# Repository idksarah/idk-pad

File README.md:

# idkpad <br>
boink 9 key macro with 2 rotary encoders and a clear window so you can see your very nice pcb :3
## usage
3d print the included files and send the idkpad/manu.zip to your preferred manufacturer

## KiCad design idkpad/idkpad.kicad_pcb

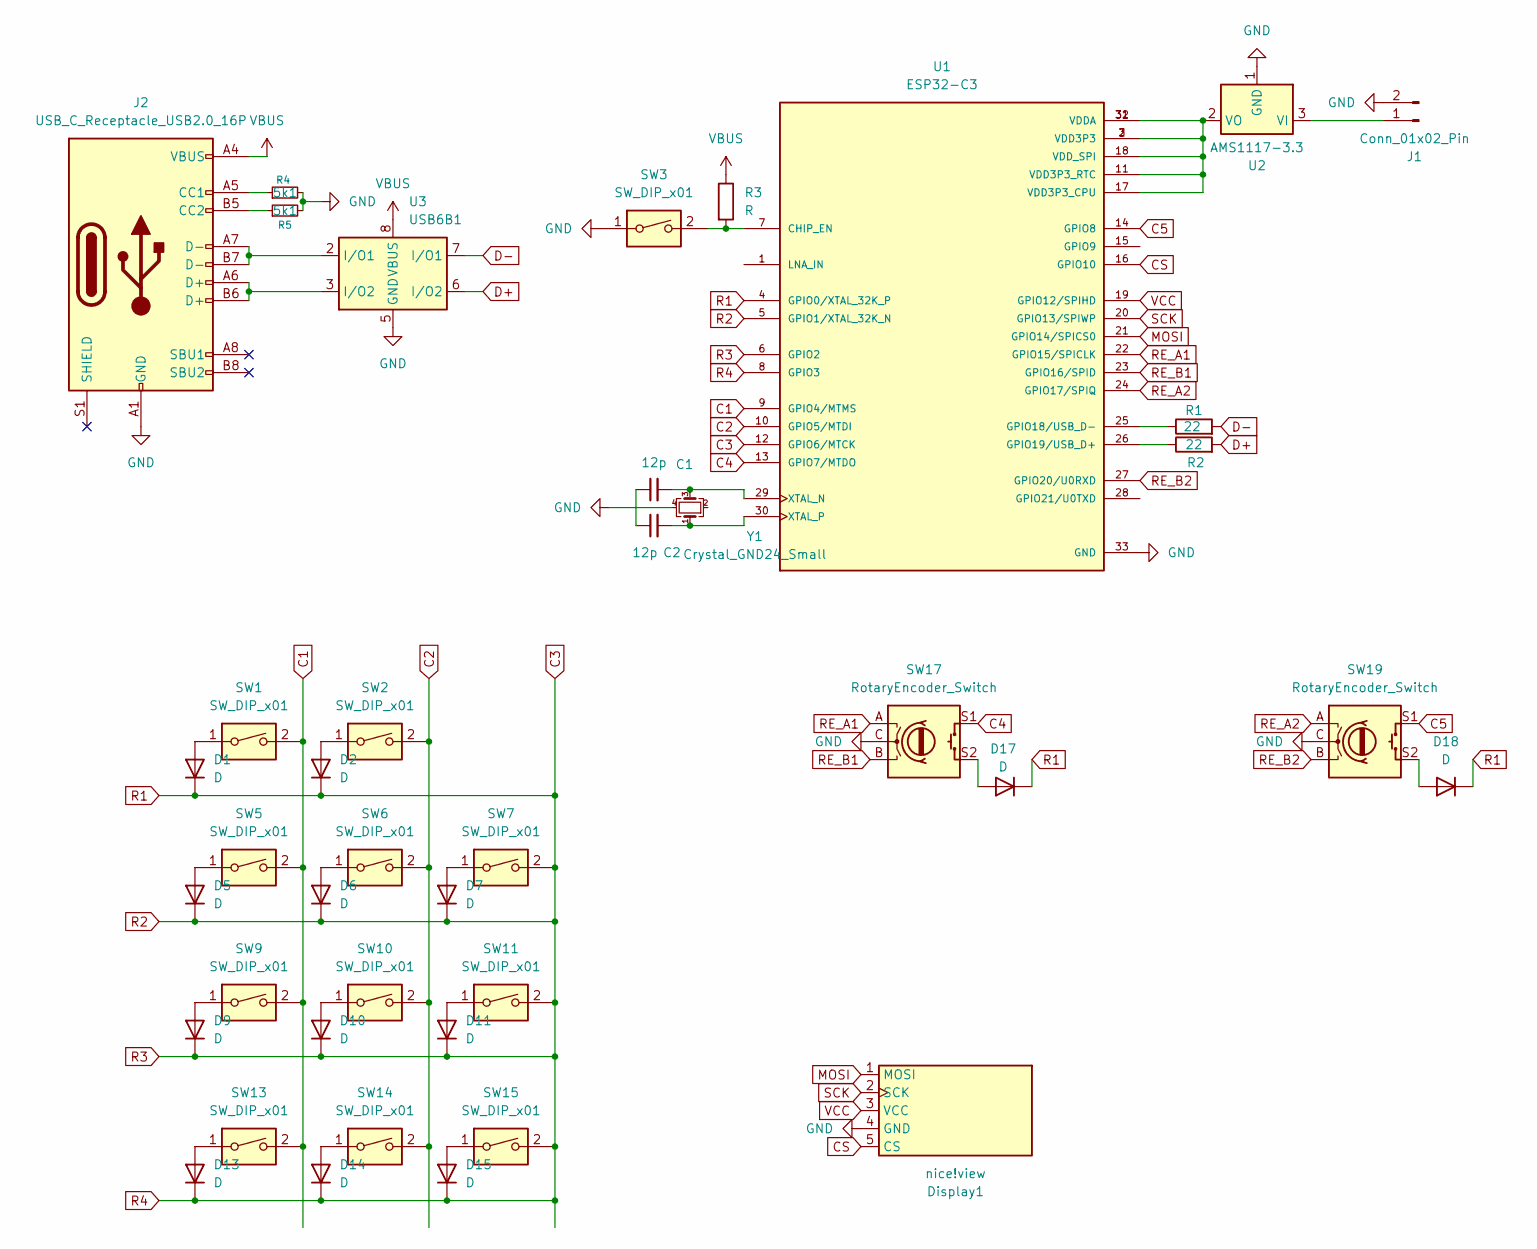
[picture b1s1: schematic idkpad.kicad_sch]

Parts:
C1, C2: 12p; CAPC1608X90
D1, D2, D5, D6, D7, D9, D10, D11, D13, D14, D15, D17, D18: D; SOD123_DIO
Display1: nice!view; nice_view
J1: Conn_01x02_Pin; JST_PH_S2B-PH-K_1x02_P2.00mm_Horizontal
J2: USB_C_Receptacle_USB2.0_16P; USB_C_Receptacle_HRO_TYPE-C-31-M-12
R1, R2: 22; R_1206_3216Metric_Pad1.30x1.75mm_HandSolder
R3: R; R_1206_3216Metric_Pad1.30x1.75mm_HandSolder
R4, R5: 5k1; R_1206_3216Metric_Pad1.30x1.75mm_HandSolder
SW1, SW2, SW3, SW5, SW6, SW7, SW9, SW10, SW11, SW13, SW14, SW15: SW_DIP_x01; Kailh_socket_MX
SW17, SW19: RotaryEncoder_Switch; RotaryEncoder_Alps_EC12E-Switch_Vertical_H20mm
U1: ESP32-C3; QFN50P500X500X90-33N; PARTREV 2.0
U2: AMS1117-3.3; SOT-223-3_TabPin2
U3: USB6B1; SOIC-8_3.9x4.9mm_P1.27mm
Y1: Crystal_GND24_Small; OSCCC320X250X90N

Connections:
C1: SW1.2, SW5.2, SW9.2, SW13.2, U1.9 (GPIO4/MTMS)
C2: SW2.2, SW6.2, SW10.2, SW14.2, U1.10 (GPIO5/MTDI)
C3: D1.1 (K), D2.1 (K), D5.1 (K), D6.1 (K), D7.1 (K), D9.1 (K), D10.1 (K), D11.1 (K), D13.1 (K), D14.1 (K), D15.1 (K), D17.1 (K), D18.1 (K), SW7.2, SW11.2, SW15.2, U1.4 (GPIO0/XTAL_32K_P), U1.5 (GPIO1/XTAL_32K_N), U1.6 (GPIO2), U1.8 (GPIO3), U1.12 (GPIO6/MTCK)
C4: SW17.S1, U1.13 (GPIO7/MTDO)
C5: SW19.S1, U1.14 (GPIO8)
CS: Display1.5 (CS), U1.16 (GPIO10)
D+: R2.2, U3.6 (I/O2)
D-: R1.2, U3.7 (I/O1)
GND: Display1.4 (GND), J1.2, J2.A1 (GND), J2.A12 (GND), J2.B1 (GND), J2.B12 (GND), R4.2, R5.2, SW3.1, SW17.C, SW19.C, U1.33 (GND), U2.1 (GND), U3.4 (GND), U3.5 (GND), Y1.4
MOSI: Display1.1 (MOSI), U1.21 (GPIO14/SPICS0)
unnamed: C1.1, C2.1
unnamed: D1.2 (A), SW1.1
unnamed: D2.2 (A), SW2.1
unnamed: D5.2 (A), SW5.1
unnamed: D6.2 (A), SW6.1
unnamed: D7.2 (A), SW7.1
unnamed: D9.2 (A), SW9.1
unnamed: D10.2 (A), SW10.1
unnamed: D11.2 (A), SW11.1
unnamed: D13.2 (A), SW13.1
unnamed: D14.2 (A), SW14.1
unnamed: D15.2 (A), SW15.1
unnamed: D17.2 (A), SW17.S2
unnamed: D18.2 (A), SW19.S2
unnamed: J1.1, U2.3 (VI)
unnamed: J2.A5 (CC1), R4.1
unnamed: J2.B5 (CC2), R5.1
unnamed: J2.A6 (D+), J2.B6 (D+), U3.3 (I/O2)
unnamed: J2.A7 (D-), J2.B7 (D-), U3.2 (I/O1)
unnamed: R3.2, SW3.2, U1.7 (CHIP_EN)
unnamed: R1.1, U1.25 (GPIO18/USB_D-)
unnamed: R2.1, U1.26 (GPIO19/USB_D+)
unnamed: U1.2 (VDD3P3), U1.3 (VDD3P3), U1.11 (VDD3P3_RTC), U1.17 (VDD3P3_CPU), U1.18 (VDD_SPI), U1.31 (VDDA), U1.32 (VDDA), U2.2 (VO)
unnamed: C1.2, U1.29 (XTAL_N), Y1.3
unnamed: C2.2, U1.30 (XTAL_P), Y1.1
RE_A1: SW17.A, U1.22 (GPIO15/SPICLK)
RE_A2: SW19.A, U1.24 (GPIO17/SPIQ)
RE_B1: SW17.B, U1.23 (GPIO16/SPID)
RE_B2: SW19.B, U1.27 (GPIO20/U0RXD)
SCK: Display1.2 (SCK), U1.20 (GPIO13/SPIWP)
VBUS: J2.A4 (VBUS), J2.A9 (VBUS), J2.B4 (VBUS), J2.B9 (VBUS), R3.1, U3.1 (VBUS), U3.8 (VBUS)
VCC: Display1.3 (VCC), U1.19 (GPIO12/SPIHD)

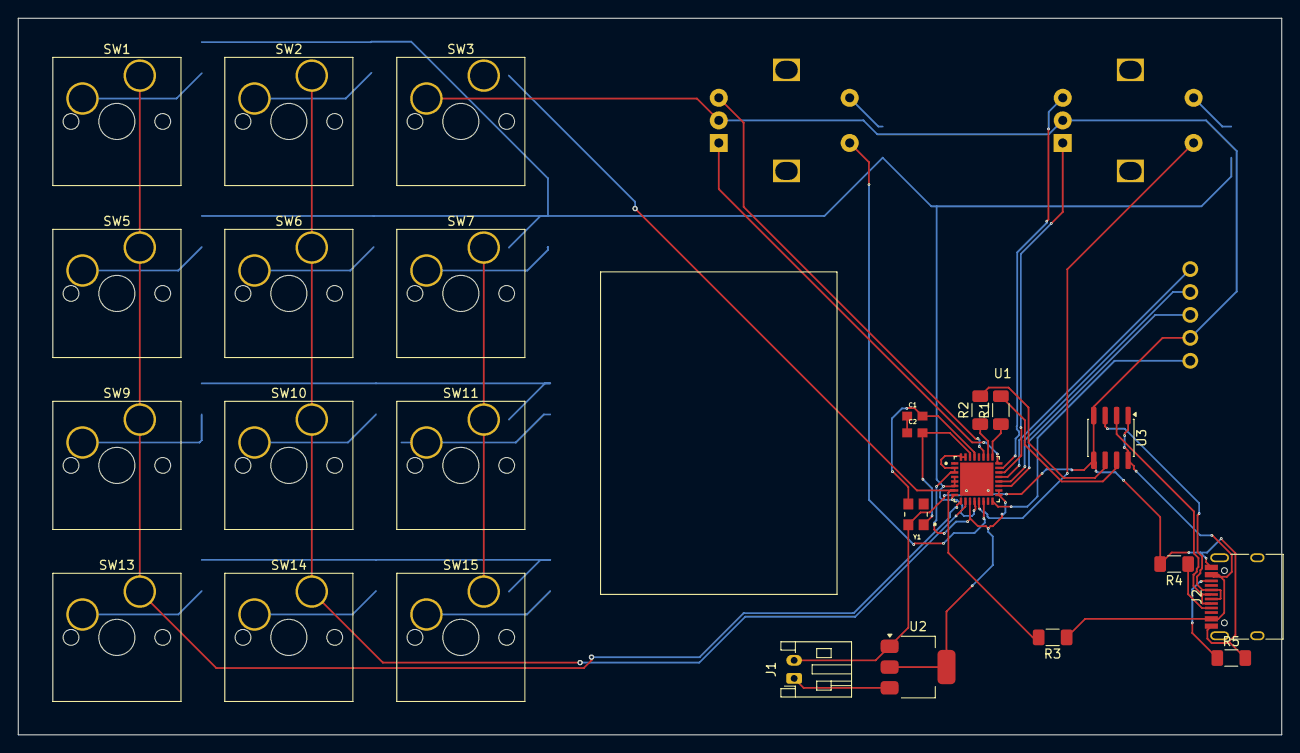
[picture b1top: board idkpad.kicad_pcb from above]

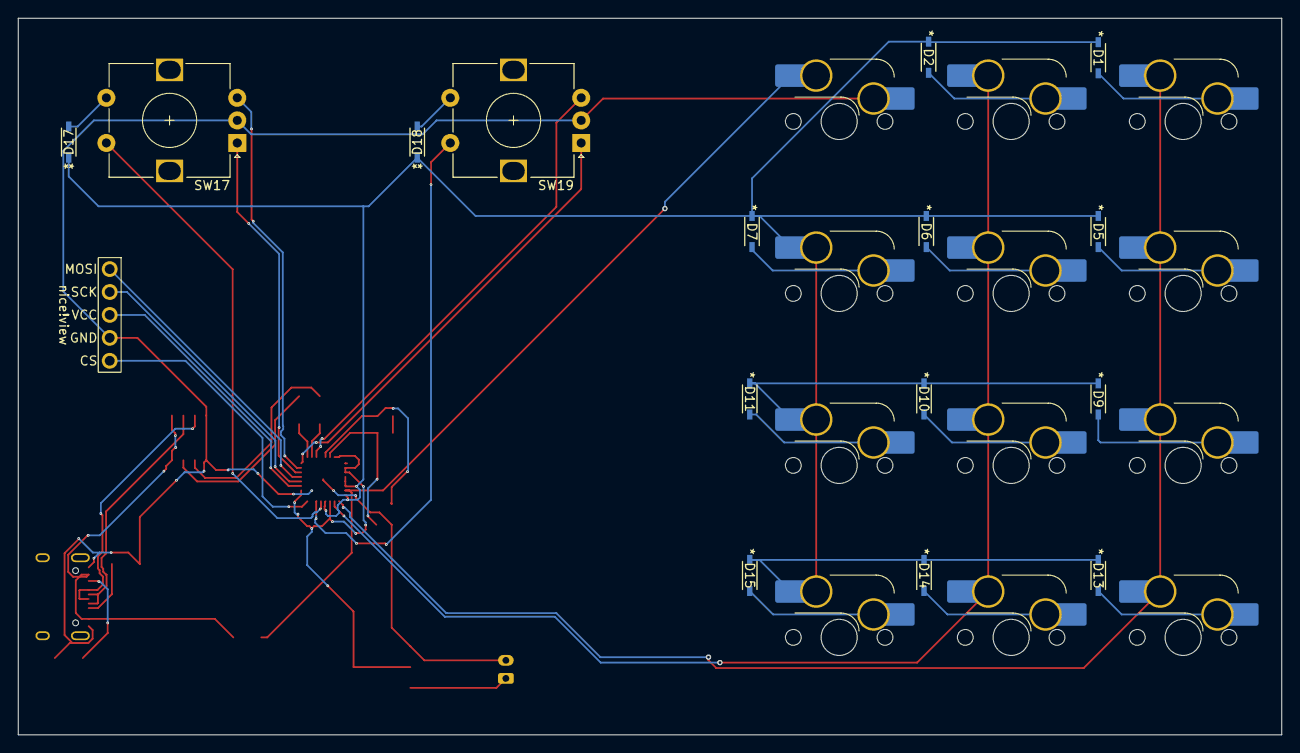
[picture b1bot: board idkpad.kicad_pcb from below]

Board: 2 copper layers, 140.0 x 79.4 mm, 41 parts (16 on the bottom side), 42 nets.

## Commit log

2025-11-03 schematic heh heh heh
2025-11-03 footprints
2025-11-03 prewiring
2025-11-03 oops i forgot to commit
2025-11-03 i forgot to save
2025-11-26 bonk
2025-11-27 Update README with usage and images
    Added usage instructions and images for idkpad.
